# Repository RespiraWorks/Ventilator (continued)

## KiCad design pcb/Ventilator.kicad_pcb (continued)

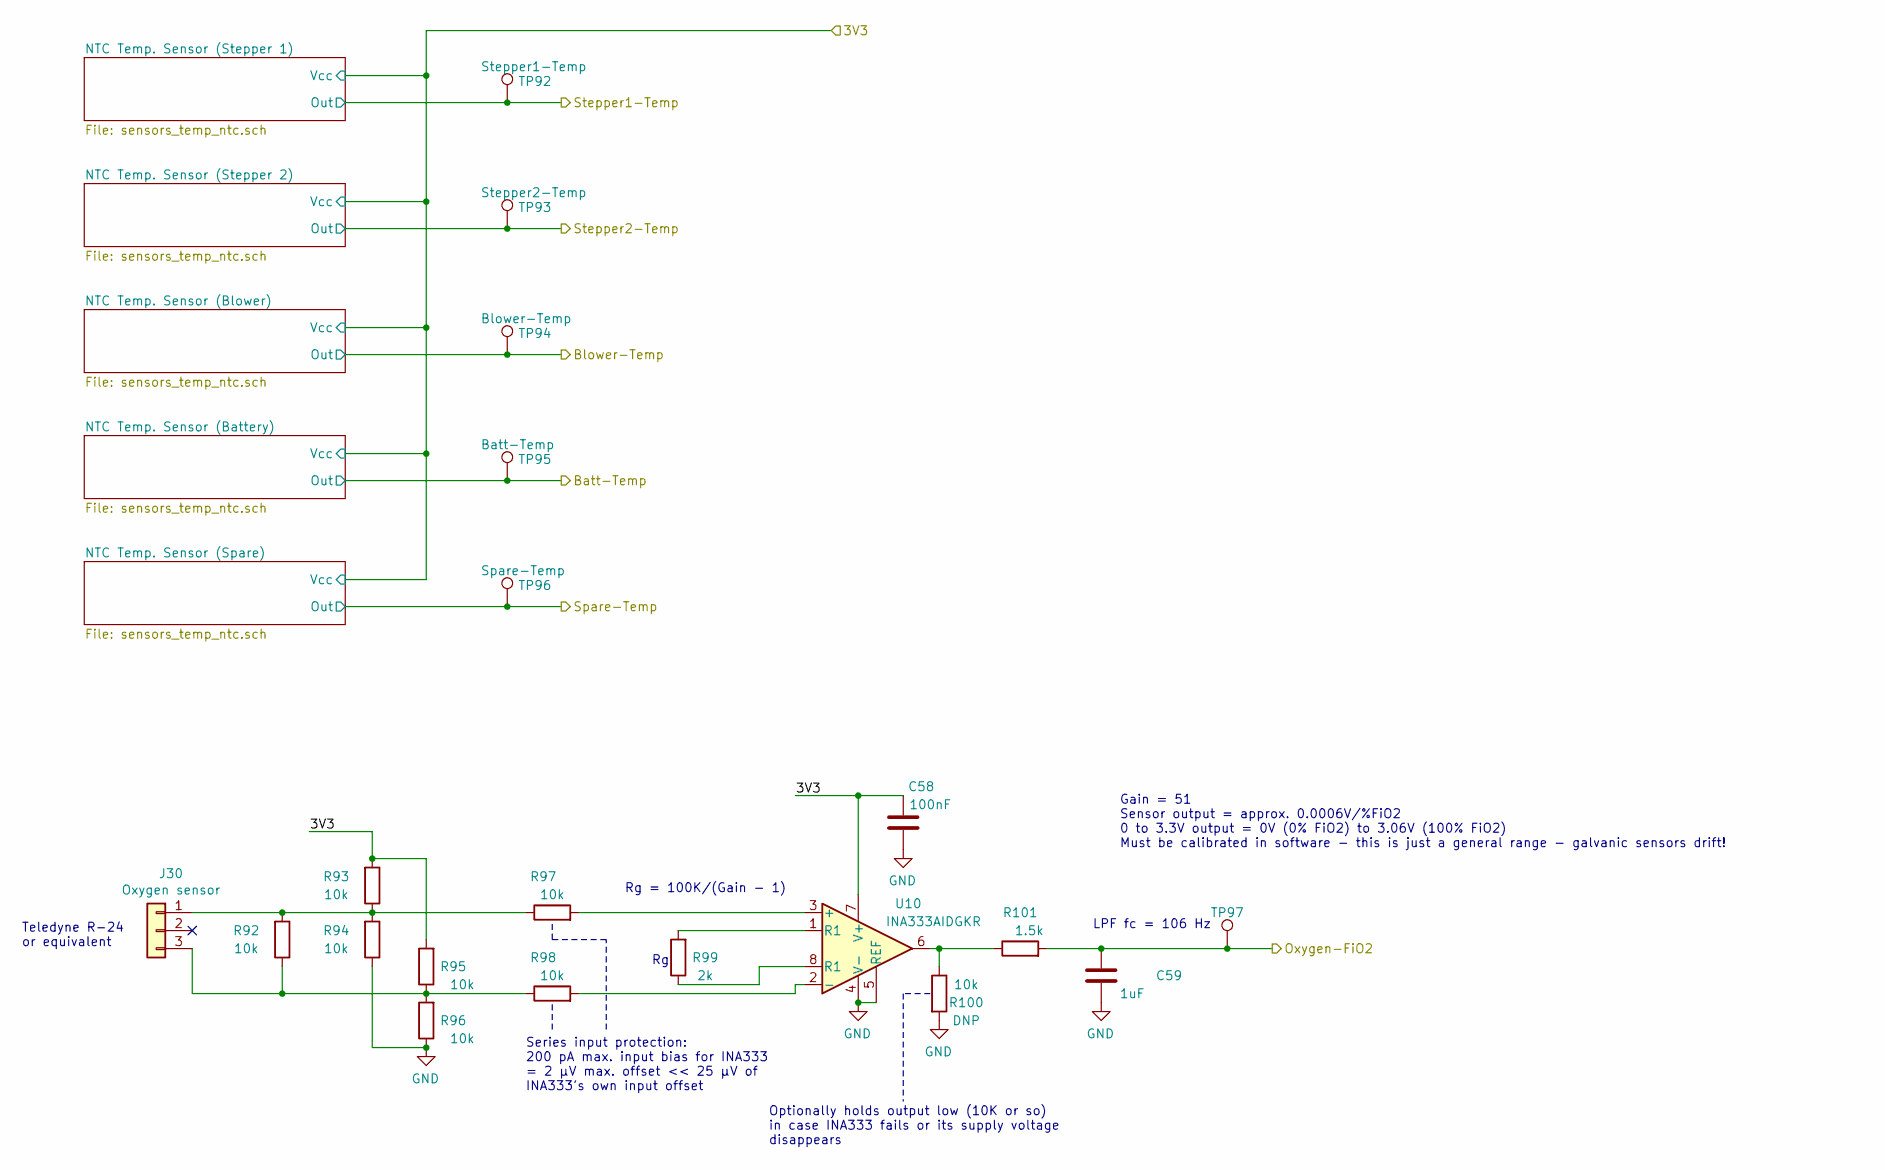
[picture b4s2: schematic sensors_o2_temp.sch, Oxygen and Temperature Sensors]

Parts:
C58: 100nF; C_0603_1608Metric; Voltage 50V; Manufacturer PN C0603C104K5RACTU
C59: 1uF; C_0603_1608Metric; Voltage 50V; Manufacturer PN C0805C105K5RACTU
J30: Oxygen sensor; Molex_Micro-Fit_3.0_43650-0315_1x03_P3.00mm_Vertical; Manufacturer PN 43650-0315
R92, R93, R94, R95, R96, R97, R98, R100: 10k; R_0603_1608Metric
R99: 2k; R_0603_1608Metric
R101: 1.5k; R_0603_1608Metric
TP92: Stepper1-Temp; TestPoint_Pad_2.0x2.0mm
TP93: Stepper2-Temp; TestPoint_Pad_2.0x2.0mm
TP94: Blower-Temp; TestPoint_Pad_2.0x2.0mm
TP95: Batt-Temp; TestPoint_Pad_2.0x2.0mm
TP96: Spare-Temp; TestPoint_Pad_2.0x2.0mm
TP97: TP; TestPoint_Pad_2.0x2.0mm
U10: INA333AIDGKR; VSSOP-8_3.0x3.0mm_P0.65mm; Manufacturer PN INA333AIDGKR

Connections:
+3.3V_Sns: C58.2, R93.2, R95.2, U10.7 (V+); also elsewhere on the board
/Oxygen-FiO2: C59.2, R101.2, TP97.1; also elsewhere on the board
/System Monitor ADC/ADC1: TP93.1; also elsewhere on the board
/System Monitor ADC/ADC2: TP94.1; also elsewhere on the board
/System Monitor ADC/ADC4: TP96.1; also elsewhere on the board
GND: C58.1, C59.1, R94.1, R96.1, R100.2, U10.4 (V-), U10.5 (REF); also elsewhere on the board
unnamed: J30.1, R92.2, R93.1, R94.2, R97.1
unnamed: J30.3, R92.1, R95.1, R96.2, R98.1
unnamed: R97.2, U10.3 (+)
unnamed: R98.2, U10.2 (-)
unnamed: R99.1, U10.8 (R1)
unnamed: R99.2, U10.1 (R1)
unnamed: R100.1, R101.1, U10.6

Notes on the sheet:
Gain = 51 Sensor output = approx. 0.0006V/%FiO2 0 to 3.3V output = 0V (0% FiO2) to 3.06V (100% FiO2) Must be calibrated in software - this is just a general range - galvanic sensors drift!
Teledyne R-24 or equivalent
LPF fc = 106 Hz
Rg = 100K/(Gain - 1)
Series input protection: 200 pA max. input bias for INA333 = 2 µV max. offset << 25 µV of INA333's own input offset
Optionally holds output low (10K or so) in case INA333 fails or its supply voltage disappears

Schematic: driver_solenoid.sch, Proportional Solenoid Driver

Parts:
C65: 10uF; C_1210_3225Metric; Voltage 100V; Manufacturer PN GRM32EC72A106KE05L
C156: 68uF; CP_Elec_8x10; Voltage 50V; Manufacturer PN UUD1H680MNL1GS
D15: 20V; D_SMC; Manufacturer PN SMBJ20AQ-13-F
D16: ES2B; D_SMA; Manufacturer PN ES2G-E3/52T
F4: 2A; Fuse_2920_Bel_fuse; Manufacturer PN 0ZCF0200AF2C
J36: Solenoid; Molex_Micro-Fit_3.0_43650-0215_1x02_P3.00mm_Vertical; Manufacturer PN 43650-0215
JP9: Jumper_NC_Small; SolderJumper-2_P1.3mm_Bridged_RoundedPad1.0x1.5mm
Q14: FDS4672A; SOIC-8_3.9x4.9mm_P1.27mm; Manufacturer PN FDS4672A
R112: 100k; R_0603_1608Metric
R113, R117: 10k; R_0603_1608Metric
R114: 52.3k; R_0603_1608Metric
R115: 1k; R_0603_1608Metric
R116: 1.5k; R_0603_1608Metric
R118: 2k; R_0603_1608Metric
R119, R120: 0; R_1206_3216Metric
TP98, TP99: TP; TestPoint_Pad_2.0x2.0mm
TP100, TP101: TestPoint_Flag; TestPoint_Keystone_5019_Minature; Manufacturer PN 5019
U16: TPS1H100A; TSSOP-14-1EP_4.4x5mm_P0.65mm; Manufacturer PN TPS1H100AQPWPRQ1

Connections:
+3.3V_Ctrl: R113.1, U16.12 (DIAG_EN); also elsewhere on the board
+VLink: C65.1, C156.1, R120.1, U16.8 (VS), U16.9 (VS), U16.10 (VS); also elsewhere on the board
/PSol2-Ctrl: R115.2, TP98.1, U16.3 (IN); also elsewhere on the board
/PSol2-nFault: JP9.1, R113.2; also elsewhere on the board
/PSol Driver, Spare/CS: R112.1, R114.1; also elsewhere on the board
GND: C65.2, C156.2, D15.2, Q14.1 (S), Q14.2 (S), Q14.3 (S), R112.2, R116.1, R117.2, R118.1, R119.2, U16.2 (GND), U16.15 (GND); also elsewhere on the board
unnamed 298: D15.1, D16.1 (K), J36.1, TP100.1; also elsewhere on the board
unnamed: D16.2 (A), J36.2, Q14.5 (D), Q14.6 (D), Q14.7 (D), Q14.8 (D), R119.1, TP101.1
unnamed 308: F4.2; also elsewhere on the board
unnamed 320: R120.2, U16.5 (OUT), U16.6 (OUT), U16.7 (OUT); also elsewhere on the board
unnamed 323: F4.1; also elsewhere on the board
unnamed: JP9.2, R114.2, R116.2, TP99.1, U16.14 (CS)
unnamed: Q14.4 (G), R115.1, R117.1
unnamed: R118.2, U16.13 (CL)

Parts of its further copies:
C66: 68uF; CP_Elec_8x10; Voltage 50V; Manufacturer PN UUD1H680MNL1GS
C155: 10uF; C_1210_3225Metric; Voltage 100V; Manufacturer PN GRM32EC72A106KE05L
D30: 20V; D_SMC; Manufacturer PN SMBJ20AQ-13-F
D31: ES2B; D_SMA; Manufacturer PN ES2G-E3/52T
F1: 2A; Fuse_2920_Bel_fuse; Manufacturer PN 0ZCF0200AF2C
J47: Solenoid; Molex_Micro-Fit_3.0_43650-0215_1x02_P3.00mm_Vertical; Manufacturer PN 43650-0215
JP13: Jumper_NC_Small; SolderJumper-2_P1.3mm_Bridged_RoundedPad1.0x1.5mm
Q26: FDS4672A; SOIC-8_3.9x4.9mm_P1.27mm; Manufacturer PN FDS4672A
R216: 100k; R_0603_1608Metric
R217, R221: 10k; R_0603_1608Metric
R218: 52.3k; R_0603_1608Metric
R219: 1k; R_0603_1608Metric
R220: 1.5k; R_0603_1608Metric
R222: 2k; R_0603_1608Metric
R223, R224: 0; R_1206_3216Metric
TP115, TP116: TP; TestPoint_Pad_2.0x2.0mm
TP117, TP118: TestPoint_Flag; TestPoint_Keystone_5019_Minature; Manufacturer PN 5019
U26: TPS1H100A; TSSOP-14-1EP_4.4x5mm_P0.65mm; Manufacturer PN TPS1H100AQPWPRQ1

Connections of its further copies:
+3.3V_Ctrl: R217.1, U26.12 (DIAG_EN); also elsewhere on the board
+VLink: C66.1, C155.1, R224.1, U26.8 (VS), U26.9 (VS), U26.10 (VS); also elsewhere on the board
/PSol1-Ctrl: R219.2, TP115.1, U26.3 (IN); also elsewhere on the board
/PSol1-nFault: JP13.1, R217.2; also elsewhere on the board
/PSol Driver/CS: R216.1, R218.1; also elsewhere on the board
GND: C66.2, C155.2, D30.2, Q26.1 (S), Q26.2 (S), Q26.3 (S), R216.2, R220.1, R221.2, R222.1, R223.2, U26.2 (GND), U26.15 (GND); also elsewhere on the board
unnamed 298: F1.2; also elsewhere on the board
unnamed 308: D30.1, D31.1 (K), J47.1, TP117.1; also elsewhere on the board
unnamed: D31.2 (A), J47.2, Q26.5 (D), Q26.6 (D), Q26.7 (D), Q26.8 (D), R223.1, TP118.1
unnamed 320: F1.1; also elsewhere on the board
unnamed 323: R224.2, U26.5 (OUT), U26.6 (OUT), U26.7 (OUT); also elsewhere on the board
unnamed: JP13.2, R218.2, R220.2, TP116.1, U26.14 (CS)
unnamed: Q26.4 (G), R219.1, R221.1
unnamed: R222.2, U26.13 (CL)

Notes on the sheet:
Protects MOSFET in case of supply overvoltage, or flyback diode failure
TPS1H100 driver option
CL voltage threshold = 1.23V CL current = Iout/2000 +/- 20% 2K = 1.23A nom. limit, 0.98 - 1.48A range 2.4K = 1.03A nom. limit, 0.82 - 1.23A range
Ics = Iout / 500 +/- 5% 853 mA = 2.56V 400 mA = 1.2V 100 mA = 0.3V
Fault voltage goes up to 4.9V; divider puts this in 3.3V ADC range Only populate if using TPS1H100B
Populate if using discrete driver
Populate if using TPS1H100 driver
Protects controller from drain-to-gate short
8.1uF @ 12V, 5.5uF @ 24V
Discrete driver option
SMBJ20AQ: 32.4V max clamping @ 18.5A
Gain of 0.657x

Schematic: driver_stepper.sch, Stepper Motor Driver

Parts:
C67, C68, C72, C77, C79: 100nF; C_0603_1608Metric; Voltage 50V; Manufacturer PN C0603C104K5RACTU
C69: 10uF; C_1210_3225Metric; Voltage 100V; Manufacturer PN GRM32EC72A106KE05L
C70, C73, C75, C78, C84: 220nF; C_0805_2012Metric; Voltage 100V; Manufacturer PN C0805C224K1RACTU
C81, C82: 68uF; CP_Elec_8x10; Voltage 50V; Manufacturer PN UUD1H680MNL1GS
C173: 10nF; C_0603_1608Metric; Voltage 50V; Manufacturer PN GRM1885C1H103JA01D
D17: Green; LED_0805_2012Metric; Manufacturer PN LTST-C171KGKT
D18, D19: BAT54J; D_SOD-323F; Manufacturer PN BAT54J,115
D20, D21, D22, D23, D24, D25: Yellow; LED_0805_2012Metric; Manufacturer PN LTST-C170KSKT
J37: Limit switch; Molex_Micro-Fit_3.0_43650-0315_1x03_P3.00mm_Vertical; Manufacturer PN 43650-0315
J38: Stepper Motor Windings; Molex_Micro-Fit_3.0_43650-0415_1x04_P3.00mm_Vertical; Manufacturer PN 43650-0415
R121, R126: 0; R_1206_3216Metric; Voltage 25V
R122, R123, R127: 0; R_0603_1608Metric
R124, R129, R130: 39k; R_0603_1608Metric
R125, R128, R131, R132, R133, R134, R135, R136: 1k; R_0603_1608Metric
TP102: nCS; TestPoint_Pad_2.0x2.0mm
TP103: StCk; TestPoint_Pad_2.0x2.0mm
TP104: SDI; TestPoint_Pad_2.0x2.0mm
TP105: CK; TestPoint_Pad_2.0x2.0mm
TP106: OscIn; TestPoint_Pad_2.0x2.0mm
TP107: OscOut; TestPoint_Pad_2.0x2.0mm
TP108: SDO; TestPoint_Pad_2.0x2.0mm
TP109: nBusy-Sync; TestPoint_Pad_2.0x2.0mm
TP110: nFlag; TestPoint_Pad_2.0x2.0mm
TP111: Out-A1; TestPoint_Pad_2.0x2.0mm
TP112: Out-A2; TestPoint_Pad_2.0x2.0mm
TP113: Out-B1; TestPoint_Pad_2.0x2.0mm
TP114: Out-B2; TestPoint_Pad_2.0x2.0mm
U27: L6470PD; ST_POWERSO36_ThermalVias; Manufacturer PN L6470PD

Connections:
+3.3V_Ctrl: C69.1, C77.1, C79.2, R121.2, R124.2, R127.2, R128.1, R129.2, R130.2, R132.2, R133.2, U27.9, U27.24; also elsewhere on the board
+12V: R126.2; also elsewhere on the board
+12V_Step1: C70.1, C73.1, C75.1, C78.1, C81.1, C82.1, C84.1, D18.2 (A), R122.2, R126.1, U27.4, U27.5, U27.15, U27.16, U27.22, U27.23, U27.33, U27.34; also elsewhere on the board
/Stepper1-StCk: R124.1, TP103.1; also elsewhere on the board
/Stepper1-nBusy: D22.1, R129.1, TP109.1; also elsewhere on the board
/Stepper2-StCk: U27.32; also elsewhere on the board
/Stepper2-nBusy: U27.29; also elsewhere on the board
/Stepper Motor Driver (..)/ADC-In: U27.8; also elsewhere on the board
/Stepper Motor Driver (..)/Out-A1: U27.2, U27.3; also elsewhere on the board
/Stepper Motor Driver (..)/Out-A2: U27.35, U27.36; also elsewhere on the board
/Stepper Motor Driver (..)/Out-B1: U27.17, U27.18; also elsewhere on the board
/Stepper Motor Driver (..)/Out-B2: U27.20, U27.21; also elsewhere on the board
/Stepper Motor Driver (..)/SDI: TP108.1, U27.27; also elsewhere on the board
/Stepper Motor Driver (..)/Switch: U27.7; also elsewhere on the board
/Stepper Motor Driver (...)/ADC-In: C67.2, R122.1, R123.2; also elsewhere on the board
/Stepper Motor Driver (...)/Out-A1: D25.2, J38.1, TP111.1; also elsewhere on the board
/Stepper Motor Driver (...)/Out-A2: D24.2, J38.2, TP112.1; also elsewhere on the board
/Stepper Motor Driver (...)/Out-B1: D23.2, J38.3, TP113.1; also elsewhere on the board
/Stepper Motor Driver (...)/Out-B2: D21.2, J38.4, TP114.1; also elsewhere on the board
/Stepper Motor Driver (...)/Switch: R125.1, R127.1; also elsewhere on the board
/Stepper-MISO: U27.25; also elsewhere on the board
/Stepper-MOSI: TP104.1; also elsewhere on the board
/Stepper-SCK: TP105.1, U27.26; also elsewhere on the board
/Stepper-nCS: TP102.1, U27.30; also elsewhere on the board
/Stepper-nFlag: D20.1, R130.1, TP110.1, U27.31; also elsewhere on the board
/Stepper-nReset: C72.2, U27.6; also elsewhere on the board
GND: C67.1, C68.1, C69.2, C70.2, C72.1, C73.2, C75.2, C77.2, C78.2, C79.1, C81.2, C82.2, D17.1, J37.1, R123.1, R131.1, R134.1, R135.1, R136.1, U27.1, U27.12, U27.19, U27.28, U27.EPAD; also elsewhere on the board
unnamed: C68.2, J37.2, R125.2
unnamed 252: C84.2, D19.1 (K); also elsewhere on the board
unnamed: C173.1, U27.13
unnamed 286: U27.14; also elsewhere on the board
unnamed: D17.2, R128.2
unnamed: D20.2, R133.1
unnamed: D21.1, R131.2
unnamed: D22.2, R132.1
unnamed: D23.1, R134.2
unnamed: D24.1, R135.2
unnamed: D25.1, R136.2
unnamed: J37.3, R121.1
unnamed 483: TP106.1; also elsewhere on the board
unnamed 484: TP107.1; also elsewhere on the board
unnamed 485: U27.10; also elsewhere on the board
unnamed 486: U27.11; also elsewhere on the board

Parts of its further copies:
C83: 10nF; C_0603_1608Metric; Voltage 50V; Manufacturer PN GRM1885C1H103JA01D
C157, C158, C162, C167, C169: 100nF; C_0603_1608Metric; Voltage 50V; Manufacturer PN C0603C104K5RACTU
C159: 10uF; C_1210_3225Metric; Voltage 100V; Manufacturer PN GRM32EC72A106KE05L
C160, C163, C165, C168, C174: 220nF; C_0805_2012Metric; Voltage 100V; Manufacturer PN C0805C224K1RACTU
C171, C172: 68uF; CP_Elec_8x10; Voltage 50V; Manufacturer PN UUD1H680MNL1GS
D32: Green; LED_0805_2012Metric; Manufacturer PN LTST-C171KGKT
D33, D34: BAT54J; D_SOD-323F; Manufacturer PN BAT54J,115
D35, D36, D37, D38, D39, D40: Yellow; LED_0805_2012Metric; Manufacturer PN LTST-C170KSKT
J48: Limit switch; Molex_Micro-Fit_3.0_43650-0315_1x03_P3.00mm_Vertical; Manufacturer PN 43650-0315
J49: Stepper Motor Windings; Molex_Micro-Fit_3.0_43650-0415_1x04_P3.00mm_Vertical; Manufacturer PN 43650-0415
R225, R230: 0; R_1206_3216Metric; Voltage 25V
R226, R227, R231: 0; R_0603_1608Metric
R228, R233, R234: 39k; R_0603_1608Metric
R229, R232, R235, R236, R237, R238, R239, R240: 1k; R_0603_1608Metric
TP119: nCS; TestPoint_Pad_2.0x2.0mm
TP120: StCk; TestPoint_Pad_2.0x2.0mm
TP121: SDI; TestPoint_Pad_2.0x2.0mm
TP122: CK; TestPoint_Pad_2.0x2.0mm
TP123: OscIn; TestPoint_Pad_2.0x2.0mm
TP124: OscOut; TestPoint_Pad_2.0x2.0mm
TP125: SDO; TestPoint_Pad_2.0x2.0mm
TP126: nBusy-Sync; TestPoint_Pad_2.0x2.0mm
TP127: nFlag; TestPoint_Pad_2.0x2.0mm
TP128: Out-A1; TestPoint_Pad_2.0x2.0mm
TP129: Out-A2; TestPoint_Pad_2.0x2.0mm
TP130: Out-B1; TestPoint_Pad_2.0x2.0mm
TP131: Out-B2; TestPoint_Pad_2.0x2.0mm
U17: L6470PD; ST_POWERSO36_ThermalVias; Manufacturer PN L6470PD

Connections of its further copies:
+3.3V_Ctrl: C159.1, C167.1, C169.2, R225.2, R228.2, R231.2, R232.1, R233.2, R234.2, R236.2, R237.2, U17.9, U17.24; also elsewhere on the board
+12V: R230.2; also elsewhere on the board
+12V_Step1: C160.1, C163.1, C165.1, C168.1, C171.1, C172.1, C174.1, D33.2 (A), R226.2, R230.1, U17.4, U17.5, U17.15, U17.16, U17.22, U17.23, U17.33, U17.34; also elsewhere on the board
/Stepper1-StCk: U17.32; also elsewhere on the board
/Stepper1-nBusy: U17.29; also elsewhere on the board
/Stepper2-StCk: R228.1, TP120.1; also elsewhere on the board
/Stepper2-nBusy: D37.1, R233.1, TP126.1; also elsewhere on the board
/Stepper Motor Driver (..)/ADC-In: C157.2, R226.1, R227.2; also elsewhere on the board
/Stepper Motor Driver (..)/Out-A1: D40.2, J49.1, TP128.1; also elsewhere on the board
/Stepper Motor Driver (..)/Out-A2: D39.2, J49.2, TP129.1; also elsewhere on the board
/Stepper Motor Driver (..)/Out-B1: D38.2, J49.3, TP130.1; also elsewhere on the board
/Stepper Motor Driver (..)/Out-B2: D36.2, J49.4, TP131.1; also elsewhere on the board
/Stepper Motor Driver (..)/SDI: TP121.1, U17.25; also elsewhere on the board
/Stepper Motor Driver (..)/Switch: R229.1, R231.1; also elsewhere on the board
/Stepper Motor Driver (...)/ADC-In: U17.8; also elsewhere on the board
/Stepper Motor Driver (...)/Out-A1: U17.2, U17.3; also elsewhere on the board
/Stepper Motor Driver (...)/Out-A2: U17.35, U17.36; also elsewhere on the board
/Stepper Motor Driver (...)/Out-B1: U17.17, U17.18; also elsewhere on the board
/Stepper Motor Driver (...)/Out-B2: U17.20, U17.21; also elsewhere on the board
/Stepper Motor Driver (...)/Switch: U17.7; also elsewhere on the board
/Stepper-MISO: TP125.1; also elsewhere on the board
/Stepper-MOSI: U17.27; also elsewhere on the board
/Stepper-SCK: TP122.1, U17.26; also elsewhere on the board
/Stepper-nCS: TP119.1, U17.30; also elsewhere on the board
/Stepper-nFlag: D35.1, R234.1, TP127.1, U17.31; also elsewhere on the board
/Stepper-nReset: C162.2, U17.6; also elsewhere on the board
GND: C157.1, C158.1, C159.2, C160.2, C162.1, C163.2, C165.2, C167.2, C168.2, C169.1, C171.2, C172.2, D32.1, J48.1, R227.1, R235.1, R238.1, R239.1, R240.1, U17.1, U17.12, U17.19, U17.28, U17.EPAD; also elsewhere on the board
unnamed: C83.1, U17.13
unnamed 252: U17.14; also elsewhere on the board
unnamed: C158.2, J48.2, R229.2
unnamed 286: C174.2, D34.1 (K); also elsewhere on the board
unnamed: D32.2, R232.2
unnamed: D35.2, R237.1
unnamed: D36.1, R235.2
unnamed: D37.2, R236.1
unnamed: D38.1, R238.2
unnamed: D39.1, R239.2
unnamed: D40.1, R240.2
unnamed: J48.3, R225.1
unnamed 483: U17.10; also elsewhere on the board
unnamed 484: U17.11; also elsewhere on the board
unnamed 485: TP123.1; also elsewhere on the board
unnamed 486: TP124.1; also elsewhere on the board

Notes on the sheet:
One 220 near each VS pin in layout
EMI filter; datasheet-recommended orientation fast-on slow-off for switch (internal pull-up on Switch = 85K typical)
Populate if switch isn't used
Space for optional fuse

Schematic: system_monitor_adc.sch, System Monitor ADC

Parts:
C90, C91, C92: 100nF; C_0603_1608Metric; Voltage 50V; Manufacturer PN C0603C104K5RACTU
C93: 1uF; C_0603_1608Metric; Voltage 50V; Manufacturer PN C0805C105K5RACTU
R158: 0; R_0603_1608Metric
R159, R161: DNP; R_0603_1608Metric
R160, R162: 10k; R_0603_1608Metric
U21: LM4120-IM5X-3.3; SOT-23-5; Manufacturer PN LM4120IM5X-3.3/NOPB
U22: ADC128D818; TSSOP-16_4.4x5mm_P0.65mm; Manufacturer PN ADC128D818CIMTX/NOPB

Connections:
+3.3V_Ctrl: C92.2, C93.2, R158.2, R159.2, R161.2, U22.5; also elsewhere on the board
+5V: C90.2, U21.3, U21.4; also elsewhere on the board
/CC-SCL: U22.3; also elsewhere on the board
/CC-SDA: U22.2; also elsewhere on the board
/PMon-PSys: U22.11; also elsewhere on the board
/SysMonADC-nINT: U22.6; also elsewhere on the board
/System Monitor ADC/ADC1: U22.15; also elsewhere on the board
/System Monitor ADC/ADC2: U22.14; also elsewhere on the board
/System Monitor ADC/ADC4: U22.12; also elsewhere on the board
/VBat-Sense: U22.10; also elsewhere on the board
/Vin-Sense: U22.9; also elsewhere on the board
GND: C90.1, C91.1, C92.1, C93.1, R160.1, R162.1, U21.2, U22.4; also elsewhere on the board
unnamed: C91.2, R158.1, U21.5, U22.1
unnamed: R159.1, R160.2, U22.7
unnamed: R161.1, R162.2, U22.8

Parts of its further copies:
C175, C176, C177: 100nF; C_0603_1608Metric; Voltage 50V; Manufacturer PN C0603C104K5RACTU
C178: 1uF; C_0603_1608Metric; Voltage 50V; Manufacturer PN C0805C105K5RACTU
R241: 0; R_0603_1608Metric
R242, R244: DNP; R_0603_1608Metric
R243, R245: 10k; R_0603_1608Metric
U28: LM4120-IM5X-3.3; SOT-23-5; Manufacturer PN LM4120IM5X-3.3/NOPB
U29: ADC128D818; TSSOP-16_4.4x5mm_P0.65mm; Manufacturer PN ADC128D818CIMTX/NOPB

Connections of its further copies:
+5V: C175.2, U28.3, U28.4; also elsewhere on the board
/FPGA's ADC/ADC0: U29.16; also elsewhere on the board
/FPGA's ADC/ADC1: U29.15; also elsewhere on the board
/FPGA's ADC/ADC2: U29.14; also elsewhere on the board
/FPGA's ADC/ADC3: U29.13; also elsewhere on the board
/FPGA's ADC/ADC4: U29.12; also elsewhere on the board
/FPGA's ADC/ADC5: U29.11; also elsewhere on the board
/FPGA's ADC/ADC6: U29.10; also elsewhere on the board
/FPGA's ADC/ADC7: U29.9; also elsewhere on the board
/FPGA's ADC/nINT: U29.6; also elsewhere on the board
/Safety FPGA/I2C-SCL-FPGA: U29.3; also elsewhere on the board
/Safety FPGA/I2C-SDA-FPGA: U29.2; also elsewhere on the board
GND: C175.1, C176.1, C177.1, C178.1, R243.1, R245.1, U28.2, U29.4; also elsewhere on the board
unnamed: C176.2, R241.1, U28.5, U29.1
unnamed: R242.1, R243.2, U29.7
unnamed: R244.1, R245.2, U29.8

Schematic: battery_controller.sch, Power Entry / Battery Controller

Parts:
C94: 33uF; CP_Elec_6.3x7.7; Voltage 50V; Manufacturer PN EEE-FK1H330XP
C95, C96: 10nF; C_0603_1608Metric; Voltage 50V; Manufacturer PN GRM1885C1H103JA01D
C97: 10uF; C_1210_3225Metric; Voltage 100V; Manufacturer PN GRM32EC72A106KE05L
D26: 20V; D_SMC; Manufacturer PN SMBJ20AQ-13-F
F2, F3: 10A; Fuseholder_Littelfuse_OMNI-BLOK-154; Manufacturer PN 0154010.DR
J44: POWER-ENTRY MegaFit 2x2; Molex_Mega-Fit_76829-0104_2x02_P5.70mm_Vertical; Manufacturer PN 768290104
J45: BAT-PWR MegaFit 2x1; Molex_Mega-Fit_76829-0102_2x01_P5.70mm_Vertical; Manufacturer PN 768290102
R163, R166: 442k; R_0603_1608Metric
R164, R165, R167, R168: 39k; R_0603_1608Metric

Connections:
+VLink: J44.3; also elsewhere on the board
/Power Entry / Battery Handling/Bat-N: C97.2, J45.1; also elsewhere on the board
/Power Entry / Battery Handling/Bat-P: C97.1, F3.2; also elsewhere on the board
/Power Entry / Battery Handling/Battery Charger / Source Switching/Pack-P: R166.1; also elsewhere on the board
/Power Entry / Battery Handling/Power-Sw-P: J44.4; also elsewhere on the board
/Power Entry / Battery Handling/Vin-Adp: C94.1, D26.1, F2.1, R163.1; also elsewhere on the board
/VBat-Sense: C96.1, R166.2, R167.1; also elsewhere on the board
/Vin-Sense: C95.1, R163.2, R164.1; also elsewhere on the board
GND: C94.2, C95.2, C96.2, D26.2, J44.1, R165.2, R168.2; also elsewhere on the board
unnamed: F2.2, J44.2
unnamed: F3.1, J45.2
unnamed: R164.2, R165.1
unnamed: R167.2, R168.1

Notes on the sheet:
12.0-16.8V
SMBJ20AQ: 32.4V max clamping @ 18.5A
Scaling of 0.15x: 22Vin = 3.3Vout 18Vin = 2.7Vout 13Vin = 1.95Vout 11Vin = 1.65Vout 240 Hz LPF
12V @ 7A

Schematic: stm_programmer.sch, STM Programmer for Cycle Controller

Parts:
C179, C180: 18pF; C_0603_1608Metric; Voltage 50V; Manufacturer PN C0603C180J5GACTU
C181, C182, C183, C184, C185: 100nF; C_0603_1608Metric; Voltage 50V; Manufacturer PN C0603C104K5RACTU
D41: Green; LED_0805_2012Metric; Manufacturer PN LTST-C171KGKT
D42: Red; LED_0805_2012Metric; Manufacturer PN LTST-C170KRKT
J50: USB B micro; USB_Mini-B_Wuerth_65100516121_Horizontal; Manufacturer PN 65100516121
J51: Backup debug in for cycle controller; PinHeader_1x06_P2.54mm_Vertical; Manufacturer PN M20-9980345
J52: Debug in for ST-LINK; PinHeader_1x06_P2.54mm_Vertical; Manufacturer PN M20-9980345
JP14, JP15, JP16, JP17, JP19: Jumper_NC_Small; SolderJumper-2_P1.3mm_Bridged_RoundedPad1.0x1.5mm
JP18: Jumper_NO_Small; SolderJumper-2_P1.3mm_Open_RoundedPad1.0x1.5mm
Q27: MMBT3904; SOT-23; Manufacturer PN MMBT3904-7-F
R246, R257, R258: 100k; R_0603_1608Metric
R247: 1.5k; R_0603_1608Metric
R248, R249: 0; R_0603_1608Metric
R250, R261: 10k; R_0603_1608Metric
R251: 39k; R_0603_1608Metric
R252, R260: 100; R_0603_1608Metric
R253, R254: 4.7k; R_0603_1608Metric
R255, R256: 1k; R_0603_1608Metric
R259: DNP; R_0603_1608Metric
U30: STM32F103CBT6; LQFP-48_7x7mm_P0.5mm; Manufacturer PN STM32F103CBT6
Y3: 8 Mhz; Crystal_SMD_HC49-SD; Manufacturer PN ABLS-8.000MHZ-B4-T

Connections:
+3.3V_Ctrl: C182.2, C183.2, C184.2, C185.2, J51.1, J52.1, JP18.1, Q27.3, R253.2, R255.1, R258.1, U30.1 (VBAT), U30.9 (VDDA), U30.24 (VDD), U30.36 (VDD), U30.48 (VDD); also elsewhere on the board
+5V_USB: J50.1, R250.2; also elsewhere on the board
/STM Programmer for cycle controller/CC-SWCLK: J51.2, JP14.1; also elsewhere on the board
/STM Programmer for cycle controller/CC-SWCLK-Out: JP14.2, U30.15 (PA5), U30.26 (PB13)
/STM Programmer for cycle controller/CC-SWDIO: J51.4, JP15.1; also elsewhere on the board
/STM Programmer for cycle controller/CC-SWDIO-Out: JP15.2, R260.2, U30.27 (PB14)
/STM Programmer for cycle controller/CC-SWO: J51.6, JP17.1; also elsewhere on the board
/STM Programmer for cycle controller/CC-SWO-Out: JP17.2, U30.31 (PA10)
/STM Programmer for cycle controller/CC-nRST: J51.5, JP16.1; also elsewhere on the board
/STM Programmer for cycle controller/CC-nRST-Out: JP16.2, U30.18 (PB0)
/STM Programmer for cycle controller/Prog-SWCLK: J52.2, U30.37 (PA14/JTCK/SWCLK)
/STM Programmer for cycle controller/Prog-SWDIO: J52.4, U30.34 (PA13/JTMS/SWDIO)
/STM Programmer for cycle controller/Prog-nRST: C181.2, J52.5, R258.2, U30.7 (~RST)
/STM Programmer for cycle controller/USB-D+: R248.1, U30.33 (PA12)
/STM Programmer for cycle controller/USB-D-: R249.2, U30.32 (PA11)
/STM Programmer for cycle controller/USB-Pwr-nEn: U30.28 (PB15)
/STM Programmer for cycle controller/VSense: R253.1, R254.2, U30.10 (PA0/WKUP)
/STM Programmer for cycle controller/nRenum-USB: R252.1, U30.38 (PA15/JTDI)
/UART-Rx-STM-Tx-STLink: U30.12 (PA2); also elsewhere on the board
/UART-Tx-STM-Rx-STLink: U30.13 (PA3); also elsewhere on the board
GND: C179.1, C180.1, C181.1, C182.1, C183.1, C184.1, C185.1, J50.5, J50.6, J51.3, J52.3, J52.6, JP19.2, R246.1, R251.1, R254.1, R256.2, R257.2, R259.1, R261.1, U30.8 (VSSA), U30.20 (PB2/BOOT1), U30.23 (VSS), U30.35 (VSS), U30.47 (VSS); also elsewhere on the board
unnamed: C179.2, U30.5 (PD0/OSCIN), Y3.1
unnamed: C180.2, U30.6 (PD1/OSCOUT), Y3.2
unnamed: D41.1 (K), D42.2 (A), U30.30 (PA9)
unnamed: D41.2 (A), R255.2
unnamed: D42.1 (K), R256.1
unnamed: J50.2, R249.1
unnamed: J50.3, R247.1, R248.2
unnamed: J50.4, R246.2
unnamed: JP18.2, JP19.1, U30.39 (PB3/JTDO)
unnamed: Q27.1, R250.1, R251.2, R252.2
unnamed: Q27.2, R247.2
unnamed: R257.1, U30.44 (BOOT0)
unnamed: R259.2, U30.3 (PC14/OSC32_IN)
unnamed: R260.1, U30.25 (PB12)
unnamed: R261.2, U30.2 (PC13)

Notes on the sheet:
High: can draw 100 mA max. from USB (will always self-power successfully) Low: can draw 300 mA max. from USB (needs to negotiate power draw)
Unsure of purpose
Board identity
Ext. voltage sense; unsure why set @ 2.5V
Cut jumpers to use an external programmer to program the cycle controller instead of this built-in programmer

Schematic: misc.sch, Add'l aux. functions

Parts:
C71, C74: 33uF; CP_Elec_6.3x7.7; Voltage 50V; Manufacturer PN EEE-FK1H330XP
C85, C86, C87, C89: 100nF; C_0603_1608Metric; Voltage 50V; Manufacturer PN C0603C104K5RACTU
C88: DNP; C_0603_1608Metric
J39: Molex Micro-Fit; Molex_Micro-Fit_3.0_43650-0415_1x04_P3.00mm_Vertical; Manufacturer PN 43650-0415
J40, J41, J42, J43: Molex Micro-Fit; Molex_Micro-Fit_3.0_43650-0515_1x05_P3.00mm_Vertical; Manufacturer PN 43650-0515
J54: BLOWER-PWR MegaFit 2x1; Molex_Mega-Fit_76829-0102_2x01_P5.70mm_Vertical; Manufacturer PN 768290102
JP10, JP11: Jumper_NC_Small; SolderJumper-2_P1.3mm_Bridged_RoundedPad1.0x1.5mm
JP12: Jumper_NO_Small; SolderJumper-2_P1.3mm_Open_RoundedPad1.0x1.5mm
Q15: MMBT3904; SOT-23; Manufacturer PN MMBT3904-7-F
R137, R138: 10k; R_0603_1608Metric
R139, R141: 1k; R_0603_1608Metric
R140, R154, R155, R156, R157: 0; R_0603_1608Metric
R142, R143, R144, R145, R146, R147, R148, R149, R150, R151, R152, R153: 4.7k; R_0603_1608Metric
U18: 24LC256T-I_MS; TSSOP-8_3x3mm_P0.65mm; Manufacturer PN 24LC256T-I/MS
U19: SN74LVC2T45DCTR; SSOP-8_2.95x2.8mm_P0.65mm; Manufacturer PN SN74LVC2T45DCTR
U20: TCA9544APWR; TSSOP-20_4.4x6.5mm_P0.65mm; Manufacturer PN TCA9544APWR

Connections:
+3.3V_Ctrl: C85.2, C86.2, C89.2, JP10.1, R142.1, R143.1, R144.1, R145.1, R146.1, R147.1, R148.1, R149.1, R150.1, R151.1, R152.1, R153.1, R154.2, R155.2, R156.2, R157.2, U18.8 (VCC), U19.1 (VCCA), U19.5 (DIR), U20.20 (VCC); also elsewhere on the board
+5V: JP11.1; also elsewhere on the board
+12V: C71.1, C74.1, J54.2; also elsewhere on the board
/Add'l aux functions/Blower-Enable: R139.2; also elsewhere on the board
/Aux-I2C-Switch-nINT: U20.17 (~INT); also elsewhere on the board
/Blower-Ctrl: R137.1, U19.2 (A1); also elsewhere on the board
/CC-SCL: U18.6 (SCL), U20.18 (SCL); also elsewhere on the board
/CC-SDA: U18.5 (SDA), U20.19 (SDA); also elsewhere on the board
GND: C71.2, C74.2, C85.1, C86.1, C87.1, C88.1, C89.1, J39.4, J40.1, J41.1, J42.1, J43.1, J54.1, Q15.2, R137.2, R138.2, R141.2, U18.3 (A2), U18.4 (VSS), U18.7 (WP), U19.4 (GND), U20.1 (A0), U20.2 (A1), U20.3 (A2), U20.10 (GND); also elsewhere on the board
unnamed: C87.2, JP11.2, JP12.1, U19.8 (VCCB)
unnamed: C88.2, J39.2, R140.1
unnamed: J39.1, JP12.2
unnamed: J39.3, Q15.3
unnamed: J40.2, R142.2, U20.6 (SC0)
unnamed: J40.3, R143.2, U20.5 (SD0)
unnamed: J40.4, R144.2, U20.4 (~INT0)
unnamed: J40.5, R154.1
unnamed: J41.2, R145.2, U20.9 (SC1)
unnamed: J41.3, R146.2, U20.8 (SD1)
unnamed: J41.4, R147.2, U20.7 (~INT1)
unnamed: J41.5, R155.1
unnamed: J42.2, R148.2, U20.13 (SC2)
unnamed: J42.3, R149.2, U20.12 (SD2)
unnamed: J42.4, R150.2, U20.11 (~INT2)
unnamed: J42.5, R156.1
unnamed: J43.2, R151.2, U20.16 (SC3)
unnamed: J43.3, R152.2, U20.15 (SD3)
unnamed: J43.4, R153.2, U20.14 (~INT3)
unnamed: J43.5, R157.1
unnamed: JP10.2, U19.3 (A2)
unnamed: Q15.1, R139.1, R141.1
unnamed: R138.1, R140.2, U19.7 (B1)

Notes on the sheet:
I2C address: 1010 000
Spot for optional fuse
Add'l I2C peripherals for prototyping/testing 1: Gnd 2: SCL 3: SDA 4: ~INT~ 5: +3.3V
I2C expander
Blower PWM control signal level shifter
EEPROM
Control output powered from internal +5V
Control output powered from motor driver's +5V
Blower control 1: +5V in 2: PWM out/Speed control voltage out 3: ~Enable~ 4: Gnd
Blower connections WM9290: Uses both ~enable~ and speed control voltage (populate PWM filter); small control connector pin 1=+5V out, 2=speed ctrl voltage, 3=gnd, 4=~enable~ WM7060: (uses same driver as WM9290) WS7040: Uses speed control voltage (populate PWM filter) TKFAN BA7050H12B: Uses PWM inpu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
Optional PWM filter to produce analog control voltage

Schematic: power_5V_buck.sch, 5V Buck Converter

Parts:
C2, C3: 10uF; C_1210_3225Metric; Voltage 100V; Manufacturer PN GRM32EC72A106KE05L
C4, C8, C9: 100nF; C_0603_1608Metric; Voltage 50V; Manufacturer PN C0603C104K5RACTU
C5: 10nF; C_0603_1608Metric; Voltage 50V; Manufacturer PN GRM1885C1H103JA01D
C6: 4.7nF; C_0603_1608Metric; Voltage 50V; Manufacturer PN C0603C472J5GACTU
C7: 18pF; C_0603_1608Metric; Voltage 50V; Manufacturer PN C0603C180J5GACTU
C10: 1uF; C_0603_1608Metric; Voltage 50V; Manufacturer PN C0805C105K5RACTU
C11, C187: 47uF; C_1210_3225Metric; Voltage 10V; Manufacturer PN GRM32ER71A476KE15L
D4: PDS760; D_PowerDI-5; Manufacturer PN PDS760-13
D5: Green; LED_0805_2012Metric; Manufacturer PN LTST-C171KGKT
L1: 15uH; L_TDK_SPM12565VT; Manufacturer PN SPM12565VT-150M-D
R23: 316k; R_0603_1608Metric
R24, R27: 52.3k; R_0603_1608Metric
R25: 249k; R_0603_1608Metric
R26: 16.9k; R_0603_1608Metric
R28: 10k; R_0603_1608Metric
R29: 2k; R_0603_1608Metric
TP59: ~Power Good; TestPoint_Pad_2.0x2.0mm
TP60: TestPoint_Flag; TestPoint_Keystone_5019_Minature; Manufacturer PN 5019
U1: TPS54561; WSON-10-1EP_4x4mm_P0.8mm_EP2.6x3mm; Manufacturer PN TPS54561DPRR

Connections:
+5V_GUI: C9.2, C10.2, C11.2, C187.2, L1.2, R27.1, R29.1, TP60.1; also elsewhere on the board
+VLink: C2.1, C3.1, C4.2, R23.1, U1.2 (VDD); also elsewhere on the board
/Logic/Control Power Supplies/5V UI Supply/Fb: R27.2, R28.1, U1.6 (FB)
/Logic/Control Power Supplies/5V UI Supply/nEnable: R23.2, R24.1, U1.3 (EN); also elsewhere on the board
GND: C2.2, C3.2, C4.1, C5.2, C6.2, C7.2, C9.1, C10.1, C11.1, C187.1, D4.2 (A), D5.1 (K), R24.2, R25.2, R28.2, U1.8 (GND), U1.11 (GNDPAD); also elsewhere on the board
unnamed: C5.1, U1.4 (SS/TR)
unnamed: C6.1, R26.2
unnamed: C7.1, R26.1, U1.7 (COMP)
unnamed: C8.1, D4.1 (K), L1.1, U1.9 (SW)
unnamed: C8.2, U1.1 (BOOT)
unnamed: D5.2 (A), R29.2
unnamed: R25.1, U1.5 (RT/CLK)
unnamed: TP59.1, U1.10 (PWRGD)

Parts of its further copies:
C14, C15: 10uF; C_1210_3225Metric; Voltage 100V; Manufacturer PN GRM32EC72A106KE05L
C16, C20, C21: 100nF; C_0603_1608Metric; Voltage 50V; Manufacturer PN C0603C104K5RACTU
C17: 10nF; C_0603_1608Metric; Voltage 50V; Manufacturer PN GRM1885C1H103JA01D
C18: 4.7nF; C_0603_1608Metric; Voltage 50V; Manufacturer PN C0603C472J5GACTU
C19: 18pF; C_0603_1608Metric; Voltage 50V; Manufacturer PN C0603C180J5GACTU
C22: 1uF; C_0603_1608Metric; Voltage 50V; Manufacturer PN C0805C105K5RACTU
C23, C188: 47uF; C_1210_3225Metric; Voltage 10V; Manufacturer PN GRM32ER71A476KE15L
D6: PDS760; D_PowerDI-5; Manufacturer PN PDS760-13
D7: Green; LED_0805_2012Metric; Manufacturer PN LTST-C171KGKT
L2: 15uH; L_TDK_SPM12565VT; Manufacturer PN SPM12565VT-150M-D
R30: 316k; R_0603_1608Metric
R31, R34: 52.3k; R_0603_1608Metric
R32: 249k; R_0603_1608Metric
R33: 16.9k; R_0603_1608Metric
R35: 10k; R_0603_1608Metric
R36: 2k; R_0603_1608Metric
TP63: ~Power Good; TestPoint_Pad_2.0x2.0mm
TP64: TestPoint_Flag; TestPoint_Keystone_5019_Minature; Manufacturer PN 5019
U3: TPS54561; WSON-10-1EP_4x4mm_P0.8mm_EP2.6x3mm; Manufacturer PN TPS54561DPRR

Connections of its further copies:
+5V: C21.2, C22.2, C23.2, C188.2, L2.2, R34.1, R36.1, TP64.1; also elsewhere on the board
+VLink: C14.1, C15.1, C16.2, R30.1, U3.2 (VDD); also elsewhere on the board
/Logic/Control Power Supplies/5V Control Supply/Fb: R34.2, R35.1, U3.6 (FB)
/Logic/Control Power Supplies/5V Control Supply/nEnable: R30.2, R31.1, U3.3 (EN)
GND: C14.2, C15.2, C16.1, C17.2, C18.2, C19.2, C21.1, C22.1, C23.1, C188.1, D6.2 (A), D7.1 (K), R31.2, R32.2, R35.2, U3.8 (GND), U3.11 (GNDPAD); also elsewhere on the board
unnamed: C17.1, U3.4 (SS/TR)
unnamed: C18.1, R33.2
unnamed: C19.1, R33.1, U3.7 (COMP)
unnamed: C20.1, D6.1 (K), L2.1, U3.9 (SW)
unnamed: C20.2, U3.1 (BOOT)
unnamed: D7.2 (A), R36.2
unnamed: R32.1, U3.5 (RT/CLK)
unnamed: TP63.1, U3.10 (PWRGD)

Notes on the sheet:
~~400 kHz fsw
~~1 mA on
Each 28.7uF @ 5V ESR = 2-10 mΩ, 10 kHz-7 Mhz (Adds zero ≥500 kHz)
8.1uF @ 12V each
3.8 ms soft-start time (10%-90%)
Turns on @ 8.1V in, turns off @ 7.0V in
Zero @ 2 kHz
Vout = 0.8V * (Rhigh+Rlow)/Rlow
Rhigh
Rlow

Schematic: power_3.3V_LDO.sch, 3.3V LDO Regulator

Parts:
C12, C13: 1uF; C_0603_1608Metric; Voltage 50V; Manufacturer PN C0805C105K5RACTU
JP4: Jumper_NC_Small; SolderJumper-2_P1.3mm_Bridged_RoundedPad1.0x1.5mm
TP61: ~Power Good; TestPoint_Pad_2.0x2.0mm
TP62: TestPoint_Flag; TestPoint_Keystone_5019_Minature; Manufacturer PN 5019
U2: LD39050PU33R; DFN-6-1EP_3x3mm_P0.95mm_EP1.75x2.5mm; Manufacturer PN LD39050PU33R

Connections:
+3.3V_Ctrl: C13.2, TP62.1, U2.4 (Vout); also elsewhere on the board
/Logic/Control Power Supplies/3.3V Logic Supply/In: C12.2, JP4.2, U2.6 (Vin); also elsewhere on the board
GND: C12.1, C13.1, U2.2 (Gnd), U2.7 (Gnd); also elsewhere on the board
unnamed: JP4.1, U2.1 (En)
unnamed: TP61.1, U2.3 (~PG)

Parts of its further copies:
C24, C25: 1uF; C_0603_1608Metric; Voltage 50V; Manufacturer PN C0805C105K5RACTU
JP5: Jumper_NC_Small; SolderJumper-2_P1.3mm_Bridged_RoundedPad1.0x1.5mm
TP65: ~Power Good; TestPoint_Pad_2.0x2.0mm
TP66: TestPoint_Flag; TestPoint_Keystone_5019_Minature; Manufacturer PN 5019
U4: LD39050PU33R; DFN-6-1EP_3x3mm_P0.95mm_EP1.75x2.5mm; Manufacturer PN LD39050PU33R

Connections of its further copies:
+3.3V_Sns: C25.2, TP66.1, U4.4 (Vout); also elsewhere on the board
+5V: C24.2, JP5.2, U4.6 (Vin); also elsewhere on the board
GND: C24.1, C25.1, U4.2 (Gnd), U4.7 (Gnd); also elsewhere on the board
unnamed: JP5.1, U4.1 (En)
unnamed: TP65.1, U4.3 (~PG)

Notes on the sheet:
Stable with 1-22µF output capacitance range (1µF "nominal" recommended)

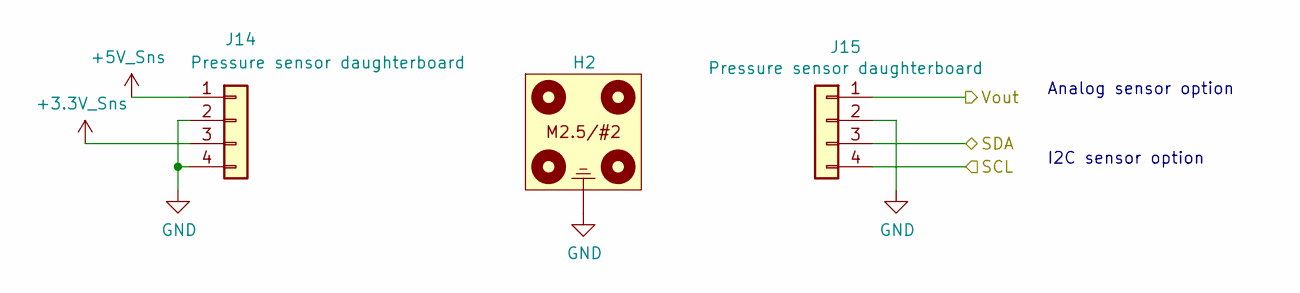
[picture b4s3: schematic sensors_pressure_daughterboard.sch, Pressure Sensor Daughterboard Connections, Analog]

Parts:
H2: Pressure_sensor_daughterboard
J14, J15: Pressure sensor daughterboard; PinHeader_1x04_P2.54mm_Vertical_SMD_Pin1Right; Manufacturer PN 87898-0424

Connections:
+3.3V_Sns: J14.3; also elsewhere on the board
+5V_Sns: J14.1; also elsewhere on the board
/CC-SCL: J15.4; also elsewhere on the board
/CC-SDA: J15.3; also elsewhere on the board
/Inh-Flow: J15.1; also elsewhere on the board
GND: H2.1, J14.2, J14.4, J15.2; also elsewhere on the board

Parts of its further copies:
H3, H4, H5, H6, H7, H8, H9: Pressure_sensor_daughterboard
J16, J17, J18, J19, J20, J21, J22, J23, J24, J25, J26, J27, J28, J29: Pressure sensor daughterboard; PinHeader_1x04_P2.54mm_Vertical_SMD_Pin1Right; Manufacturer PN 87898-0424

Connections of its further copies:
+3.3V_Sns: J16.3, J18.3, J20.3, J22.3, J24.3, J26.3, J28.3; also elsewhere on the board
+5V_Sns: J16.1, J18.1, J20.1, J22.1, J24.1, J26.1, J28.1; also elsewhere on the board
/CC-SCL: J17.4, J19.4, J21.4, J23.4, J25.4, J27.4, J29.4; also elsewhere on the board
/CC-SDA: J17.3, J19.3, J21.3, J23.3, J25.3, J27.3, J29.3; also elsewhere on the board
/Exh-Flow: J17.1; also elsewhere on the board
/Mix-Tank-Pressure: J21.1; also elsewhere on the board
/Oxygen-Flow: J19.1; also elsewhere on the board
/Oxygen-Pressure: J25.1; also elsewhere on the board
/Patient-Pressure: J23.1; also elsewhere on the board
/Pressure Sensors/Pressure sensor daughterboard (??)/Vout: J29.1
/Pressure Sensors/Pressure sensor daughterboard (Ambient)/Vout: J27.1
GND: H3.1, H4.1, H5.1, H6.1, H7.1, H8.1, H9.1, J16.2, J16.4, J17.2, J18.2, J18.4, J19.2, J20.2, J20.4, J21.2, J22.2, J22.4, J23.2, J24.2, J24.4, J25.2, J26.2, J26.4, J27.2, J28.2, J28.4, J29.2; also elsewhere on the board

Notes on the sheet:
Analog sensor option
I2C sensor option
